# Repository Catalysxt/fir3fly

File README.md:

# fir3fly
This is an enlarged 4-digit 7-segment display. The motivation is to track my boxing sessions.

- [Interactive HTML BOM](https://Catalysxt.github.io/fir3fly/ibom_v2.html)

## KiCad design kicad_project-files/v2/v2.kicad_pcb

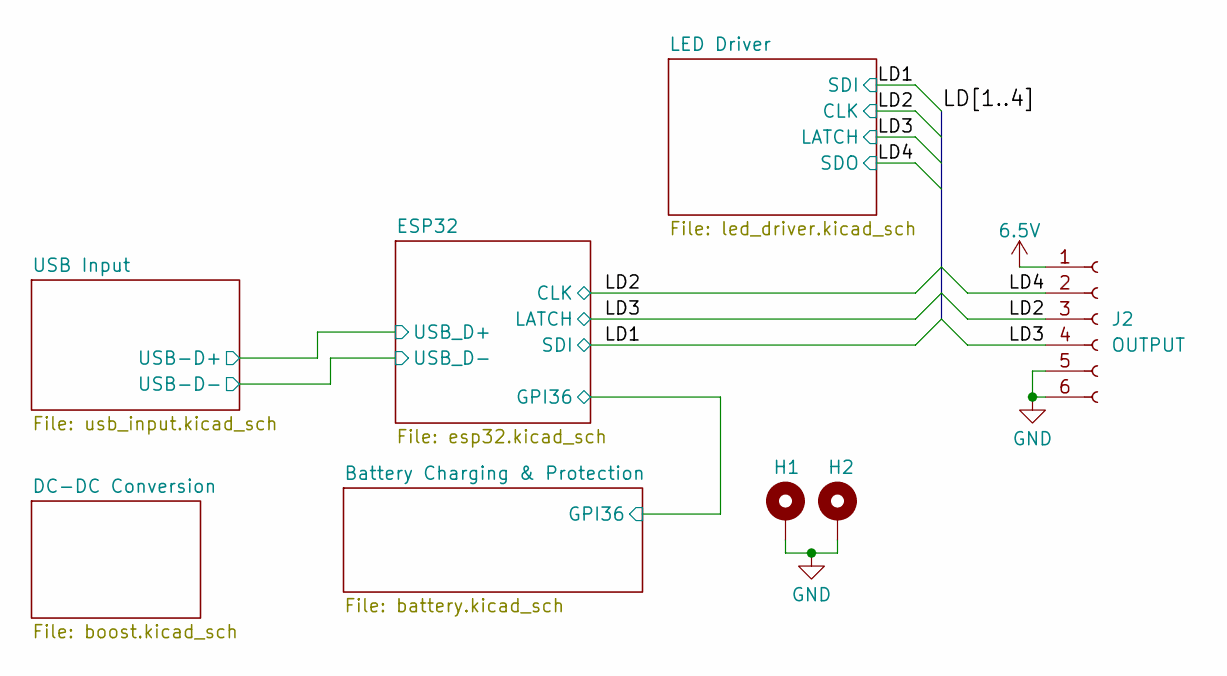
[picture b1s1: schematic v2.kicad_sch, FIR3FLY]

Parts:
H1, H2: MountingHole_Pad; MountingHole_2.5mm_Pad
J2: OUTPUT; PinSocket_1x06_P2.54mm_Horizontal

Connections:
/6.5V: J2.1
/LD2: J2.3; also elsewhere on the board
/LD3: J2.4; also elsewhere on the board
/LD4: J2.2; also elsewhere on the board
GND: H1.1 (1_1), H2.1 (1_1), J2.5, J2.6; also elsewhere on the board

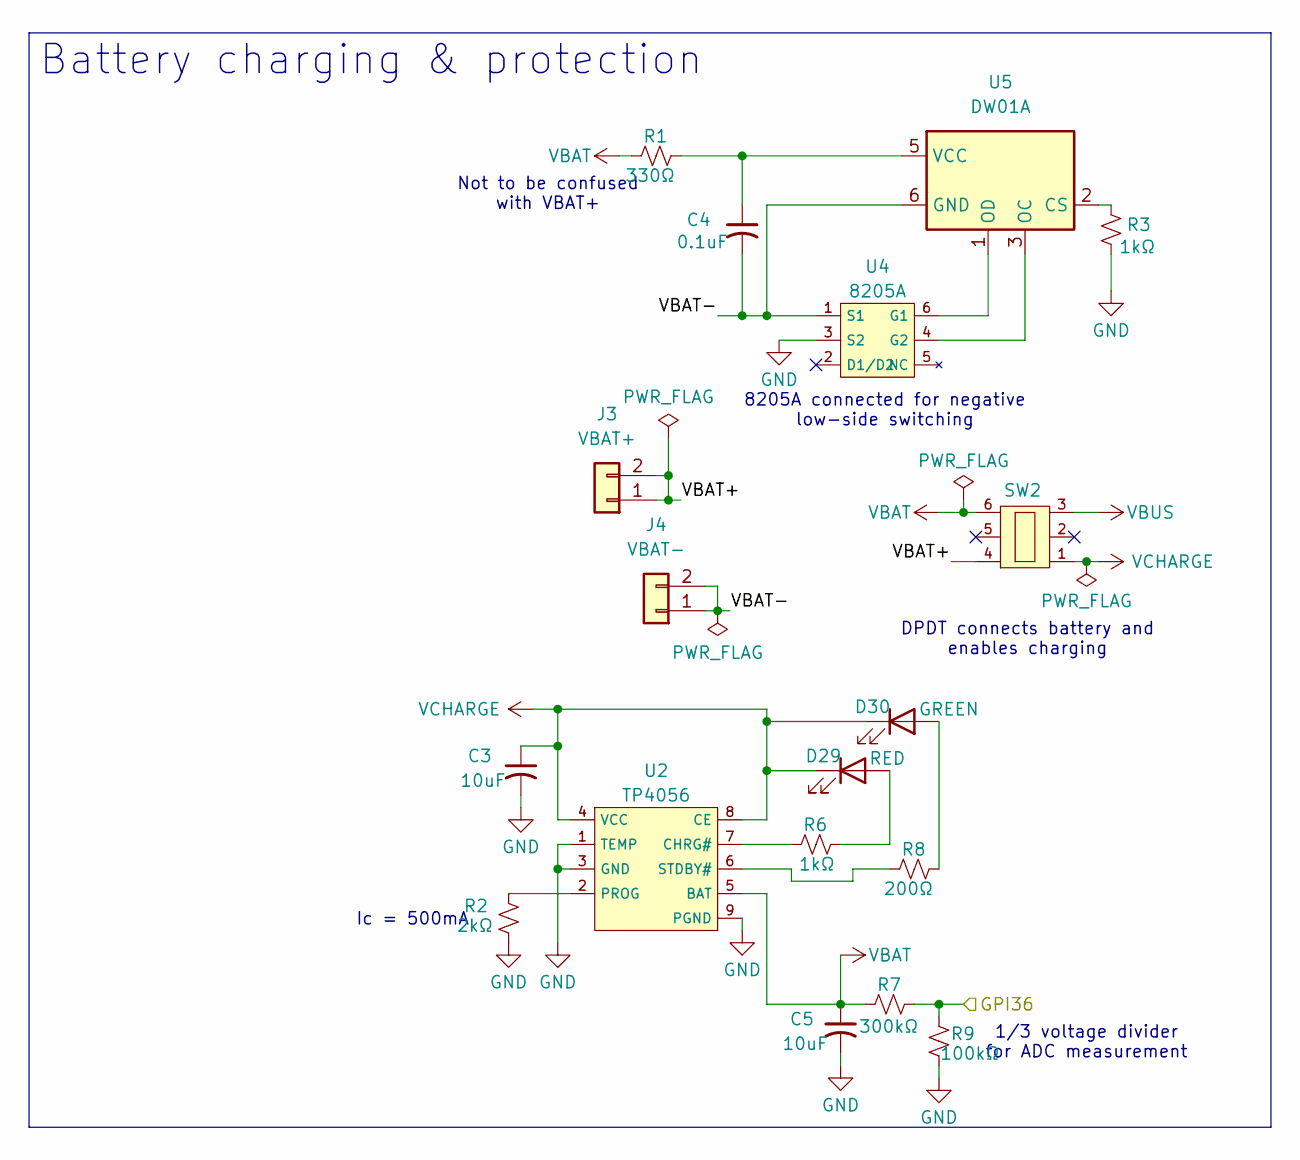
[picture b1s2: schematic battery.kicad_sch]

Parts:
C3, C5: 10uF; Taiyo Yuden TMK107BBJ106MA-T; Voltage Rating 25V; Part Type Basic; JLCPCB Part # C96446
C4: 0.1uF; C1206; Voltage Rating 50V; Part Type Basic; JLCPCB Part # C24497
D29: RED; LED_0805_Red; Part Type Basic; JLCPCB Part # C84256
D30: GREEN; LED_0805_Green; Part Type Extended; JLCPCB Part # C84260
J3: VBAT+; 18650 Battery Clip; Part Type Extended; JLCPCB Part # C2979182
J4: VBAT-; 18650 Battery Clip; Part Type Extended; JLCPCB Part # C2979182
R1: 330Ω; R_0603_1608Metric; Part Type Basic; JLCPCB Part # C23138
R2: 2kΩ; R_0603_1608Metric; Part Type Basic; JLCPCB Part # C22975
R3, R6: 1kΩ; R_0603_1608Metric; Part Type Basic; JLCPCB Part # C21190
R7: 300kΩ; R_0603_1608Metric; JLCPCB Part # C23024
R8: 200Ω; R_0603_1608Metric; Part Type Basic; JLCPCB Part # C8218
R9: 100kΩ; R_0603_1608Metric; Part Type Basic; JLCPCB Part # C25803
SW2: DPDT SW; Part Type Extended; JLCPCB Part # C22470282
U2: TP4056; ESOP-8_L4.9-W3.9-P1.27-LS6.0-BL-EP; Part Type Extended; LCSC Part # C5311018
U4: 8205A; 8205A_SOT-23-6_L2.9-W1.6-P0.95-LS2.8-BR; JLCPCB Part # C2762931
U5: DW01A; SOT-23-6

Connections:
/Battery Charging & Protection/GPI36: R7.2, R9.2; also elsewhere on the board
/Battery Charging & Protection/VBAT+: J3.1, J3.2, SW2.4
/Battery Charging & Protection/VBAT-: C4.2, J4.1, J4.2, U4.1 (S1), U5.6 (GND)
GND: C3.2, C5.2, R2.1, R3.2, R9.1, U2.1 (TEMP), U2.3 (GND), U2.9 (PGND), U4.3 (S2); also elsewhere on the board
unnamed: D29.2 (A), R6.2
unnamed: D30.2 (A), R8.2
unnamed: R6.1, U2.7 (CHRG#)
unnamed: R2.2, U2.2 (PROG)
unnamed: R8.1, U2.6 (STDBY#)
unnamed: U4.6 (G1), U5.1 (OD)
unnamed: U4.4 (G2), U5.3 (OC)
unnamed: R3.1, U5.2 (CS)
unnamed: C4.1, R1.2, U5.5 (VCC)
VBAT: C5.1, R1.1, R7.1, SW2.6, U2.5 (BAT); also elsewhere on the board
VBUS: SW2.3; also elsewhere on the board
VCHARGE: C3.1, D29.1 (K), D30.1 (K), SW2.1, U2.4 (VCC), U2.8 (CE)

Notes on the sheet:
8205A connected for negative low-side switching
DPDT connects battery and enables charging
Not to be confused with VBAT+
Ic = 500mA
1/3 voltage divider for ADC measurement
Battery charging & protection

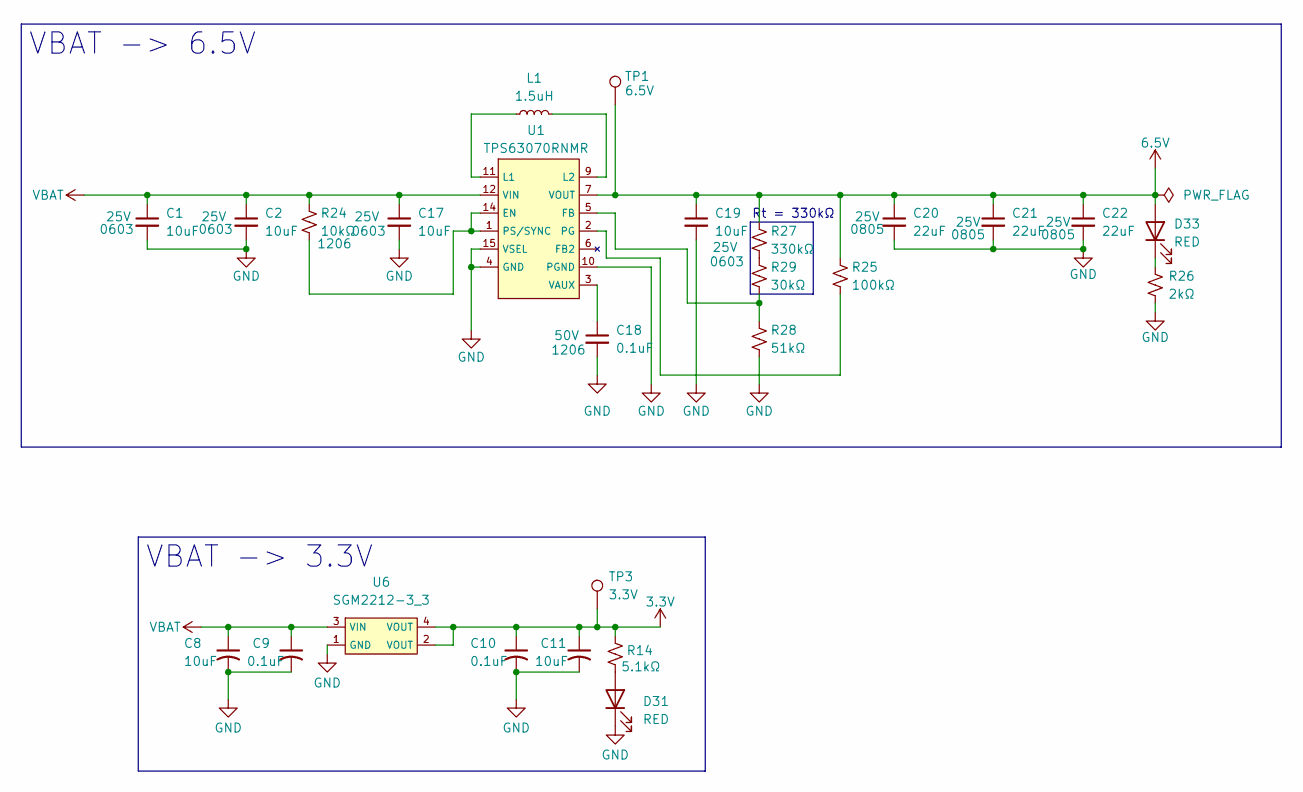
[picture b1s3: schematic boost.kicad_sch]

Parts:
C1, C2, C8, C11, C17, C19: 10uF; Taiyo Yuden TMK107BBJ106MA-T; Voltage Rating 25V; Part Type Basic; JLCPCB Part # C96446
C9, C10, C18: 0.1uF; C1206; Voltage Rating 50V; Part Type Basic; JLCPCB Part # C24497
C20, C21, C22: 22uF; C0805; Voltage Rating 25V; JLCPCB Part # C45783
D31, D33: RED; LED_0805_Red; Part Type Basic; JLCPCB Part # C84256
L1: 1.5uH; Coilcraft XFL4020-152MEC; Part Type Extended; JLCPCB Part # C3033018
R14: 5.1kΩ; R_0603_1608Metric; Part Type Basic; JLCPCB Part # C23186
R24: 10kΩ; R_0603_1608Metric; JLCPCB Part # C25804
R25: 100kΩ; R_0603_1608Metric; Part Type Basic; JLCPCB Part # C25803
R26: 2kΩ; R_0603_1608Metric
R27: 330kΩ; 0603_SMD; Part Type Basic; JLCPCB Part # C23137
R28: 51kΩ; 0603_SMD; Part Type Basic; JLCPCB Part # C23196
R29: 30kΩ; 0603_SMD; Part Type Basic; JLCPCB Part # C22984
TP1: 6.5V; TestPoint_Pad_D1.5mm
TP3: 3.3V; TestPoint_Pad_D1.5mm
U1: TPS63070RNMR; TPS63070; LCSC C109322
U6: SGM2212-3_3; SOT-223-3

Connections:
3.3V: C10.1, C11.1, R14.1, TP3.1 (1_1), U6.2 (VOUT), U6.4 (VOUT); also elsewhere on the board
6.5V: C19.1, C20.1, C21.1, C22.1, D33.2 (A), R25.1, R27.1, TP1.1 (1_1), U1.7 (VOUT); also elsewhere on the board
GND: C1.2, C2.2, C8.2, C9.2, C10.2, C11.2, C17.2, C18.2, C19.2, C20.2, C21.2, C22.2, D31.1 (K), R26.2, R28.2, U1.4 (GND), U1.10 (PGND), U1.15 (VSEL), U6.1 (GND); also elsewhere on the board
unnamed: D31.2 (A), R14.2
unnamed: D33.1 (K), R26.1
unnamed: R27.2, R29.1
unnamed: R24.2, U1.1 (PS/SYNC), U1.14 (EN)
unnamed: R28.1, R29.2, U1.5 (FB)
unnamed: L1.1, U1.11 (L1)
unnamed: L1.2, U1.9 (L2)
unnamed: R25.2, U1.2 (PG)
unnamed: C18.1, U1.3 (VAUX)
VBAT: C1.1, C2.1, C8.1, C9.1, C17.1, R24.1, U1.12 (VIN), U6.3 (VIN); also elsewhere on the board

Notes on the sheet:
Rt = 330kΩ
VBAT -> 3.3V
VBAT -> 6.5V

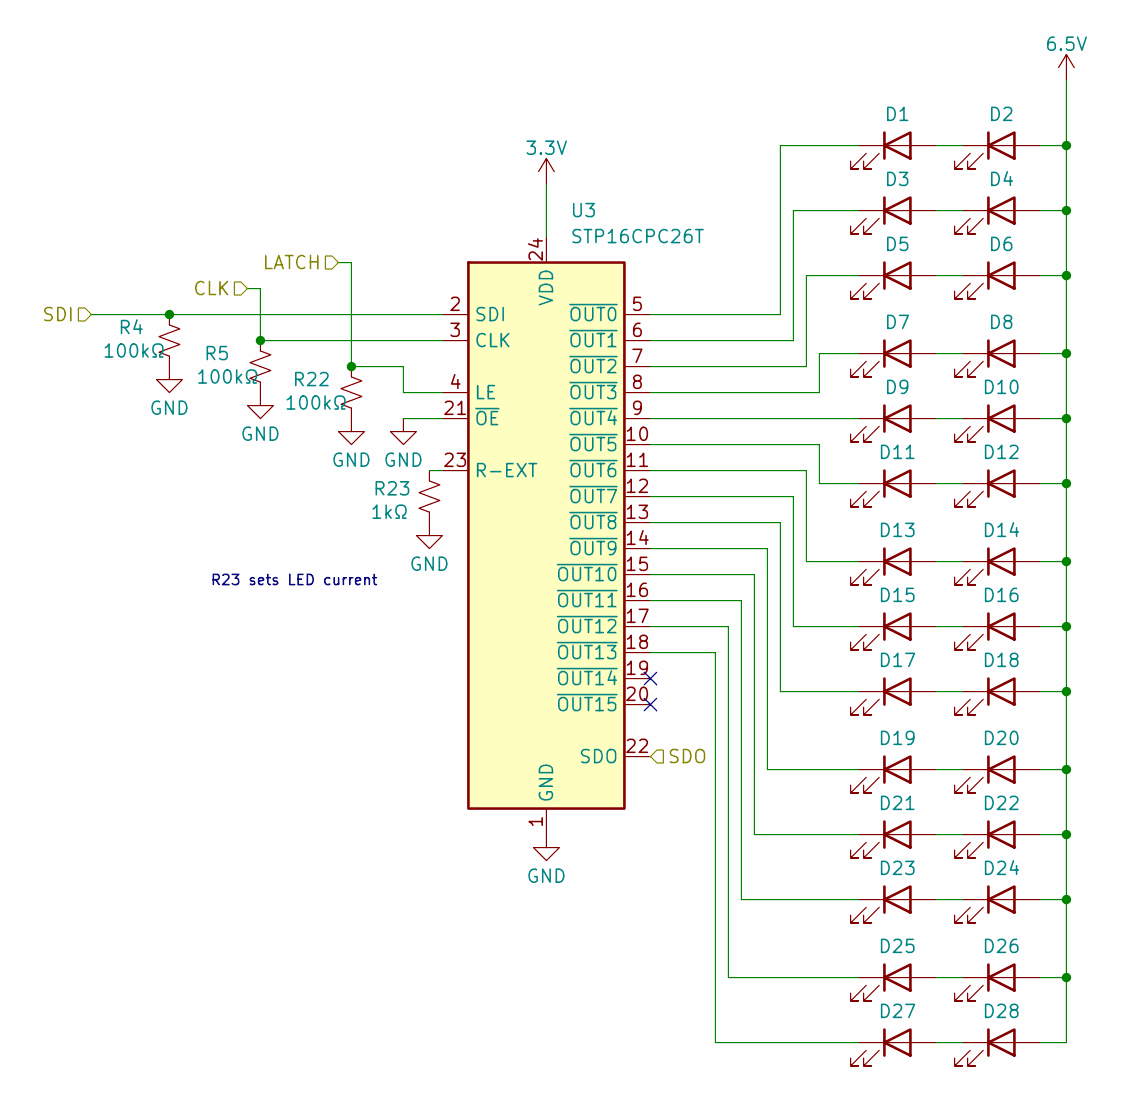
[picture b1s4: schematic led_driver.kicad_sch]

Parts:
D1: LED; LED-SMD_3P-L5.7-W3.0-RD; Part Type Extended; JLCPCB Part # C210347
D2, D3, D4, D5, D6, D7, D8, D9, D10, D11, D12, D13, D14, D15, D16, D17, D18, D19, D20, D21, D22, D23, D24, D25, D26, D27, D28: LED; LED-SMD_3P-L5.7-W3.0-RD; JLCPCB Part # C210347
R4, R5, R22: 100kΩ; R_0603_1608Metric; Part Type Basic; JLCPCB Part # C25803
R23: 1kΩ; R_0603_1608Metric; Part Type Basic; JLCPCB Part # C21190
U3: STP16CPC26T; TSSOP-24_4.4x7.8mm_P0.65mm

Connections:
3.3V: U3.24 (VDD); also elsewhere on the board
6.5V: D2.2 (A), D4.2 (A), D6.2 (A), D8.2 (A), D10.2 (A), D12.2 (A), D14.2 (A), D16.2 (A), D18.2 (A), D20.2 (A), D22.2 (A), D24.2 (A), D26.2 (A), D28.2 (A); also elsewhere on the board
/LD1: R4.1, U3.2 (SDI); also elsewhere on the board
/LD2: R5.1, U3.3 (CLK); also elsewhere on the board
/LD3: R22.1, U3.4 (LE); also elsewhere on the board
/LD4: U3.22 (SDO); also elsewhere on the board
GND: R4.2, R5.2, R22.2, R23.2, U3.1 (GND), U3.21 (~OE); also elsewhere on the board
unnamed: D1.2 (A), D2.1 (K)
unnamed: D1.1 (K), U3.5 (~OUT0)
unnamed: D3.2 (A), D4.1 (K)
unnamed: D3.1 (K), U3.6 (~OUT1)
unnamed: D5.2 (A), D6.1 (K)
unnamed: D5.1 (K), U3.7 (~OUT2)
unnamed: D7.2 (A), D8.1 (K)
unnamed: D7.1 (K), U3.8 (~OUT3)
unnamed: D9.1 (K), U3.9 (~OUT4)
unnamed: D9.2 (A), D10.1 (K)
unnamed: D11.2 (A), D12.1 (K)
unnamed: D11.1 (K), U3.10 (~OUT5)
unnamed: D13.2 (A), D14.1 (K)
unnamed: D13.1 (K), U3.11 (~OUT6)
unnamed: D15.2 (A), D16.1 (K)
unnamed: D15.1 (K), U3.12 (~OUT7)
unnamed: D17.2 (A), D18.1 (K)
unnamed: D17.1 (K), U3.13 (~OUT8)
unnamed: D19.2 (A), D20.1 (K)
unnamed: D19.1 (K), U3.14 (~OUT9)
unnamed: D21.2 (A), D22.1 (K)
unnamed: D21.1 (K), U3.15 (~OUT10)
unnamed: D23.2 (A), D24.1 (K)
unnamed: D23.1 (K), U3.16 (~OUT11)
unnamed: D25.2 (A), D26.1 (K)
unnamed: D25.1 (K), U3.17 (~OUT12)
unnamed: D27.2 (A), D28.1 (K)
unnamed: D27.1 (K), U3.18 (~OUT13)
unnamed: R23.1, U3.23 (R-EXT)

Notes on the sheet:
R23 sets LED current

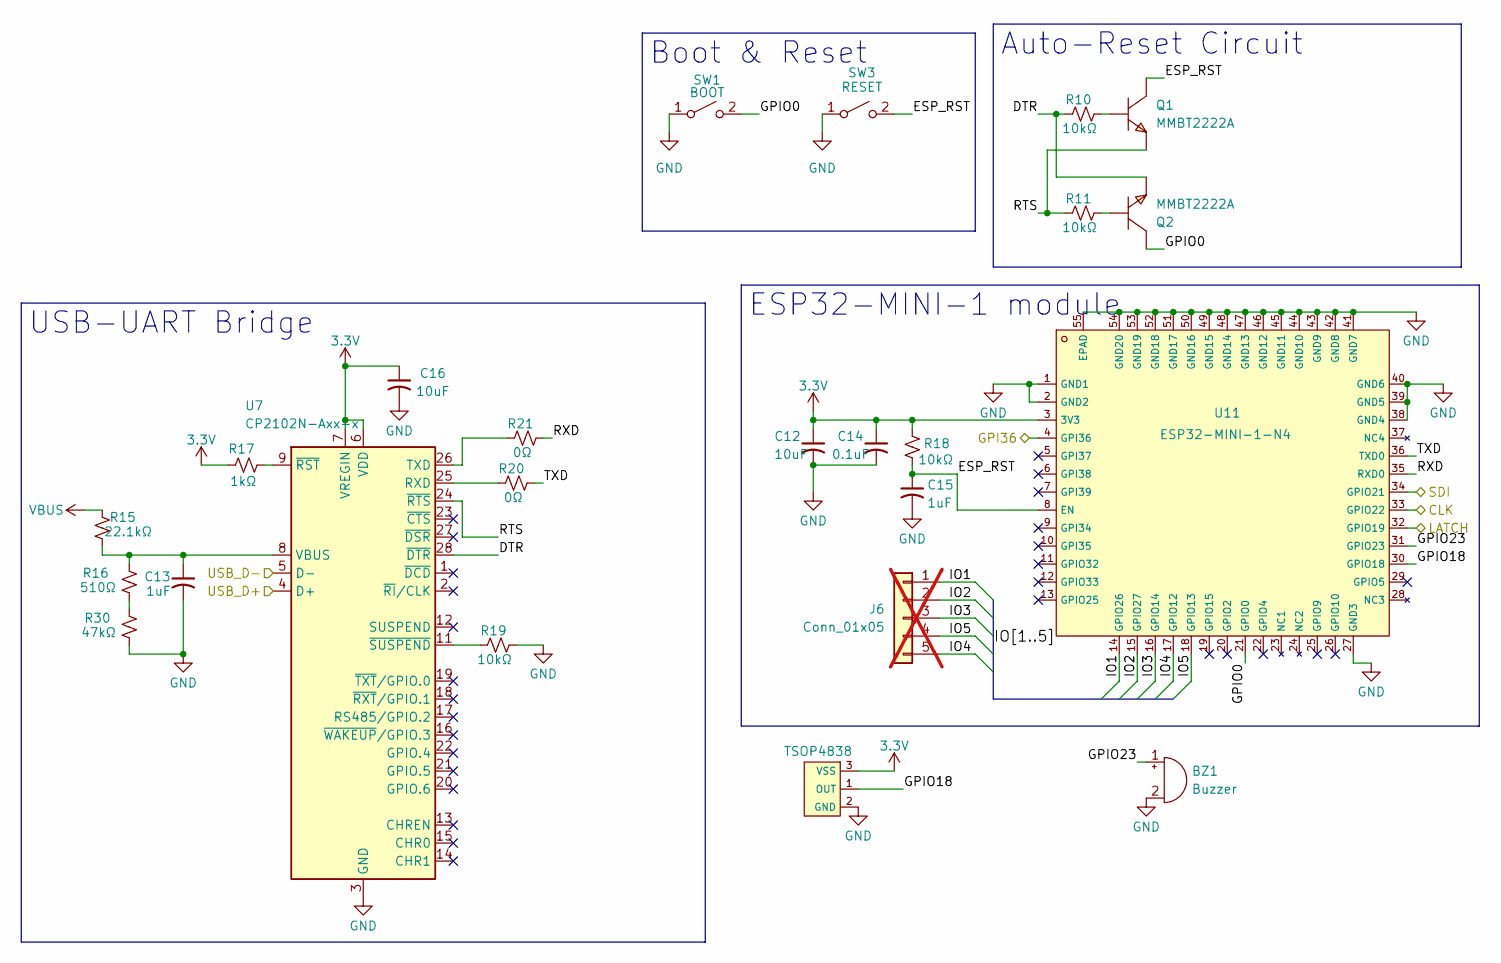
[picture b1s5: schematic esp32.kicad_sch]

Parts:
BZ1: Buzzer; BUZ-SMD_L9.6-W9.6-LS10.0-R; JLCPCB Part # C96127
C12, C16: 10uF; Taiyo Yuden TMK107BBJ106MA-T; Voltage Rating 25V; Part Type Basic; JLCPCB Part # C96446
C13, C15: 1uF; C1206; Voltage Rating 50V; Part Type Basic; JLCPCB Part # C1848
C14: 0.1uF; C1206; Voltage Rating 50V; Part Type Basic; JLCPCB Part # C24497
CGQ1: TSOP4838; JLCPCB Part # C124647
J6: Conn_01x05; PinSocket_1x05_P2.54mm_Vertical; not fitted
Q1, Q2: MMBT2222A; SOT-23-3_L2.9-W1.3-P1.90-LS2.4-BR; Part Type Basic; JLCPCB Part # C8512
R10, R11, R18: 10kΩ; R_0603_1608Metric; JLCPCB Part # C25804
R15: 22.1kΩ; R_0603_1608Metric; Part Type Basic; JLCPCB Part # C31850
R16: 510Ω; R_0603_1608Metric; Part Type Basic; JLCPCB Part # C23193
R17: 1kΩ; R_0603_1608Metric; Part Type Basic; JLCPCB Part # C21190
R19: 10kΩ; R_0603_1608Metric
R20, R21: 0Ω; 0603_SMD; Voltage Rating 0603; JLCPCB Part # C21189
R30: 47kΩ; R_0603_1608Metric; JLCPCB Part # C25819
SW1: BOOT; SW-SMD_L3.9-W3.0-P4.45; JLCPCB Part # C720477
SW3: RESET; SW-SMD_L3.9-W3.0-P4.45; JLCPCB Part # C720477
U7: CP2102N-Axx-x; QFN-28-1EP_5x5mm_P0.5mm_EP3.35x3.35mm
U11: ESP32-MINI-1-N4; ESP32-MINI-1 Module

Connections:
3.3V: C12.1, C14.1, C16.1, CGQ1.3 (VSS), R17.1, R18.1, U7.6 (VDD), U7.7 (VREGIN), U11.3 (3V3); also elsewhere on the board
/Battery Charging & Protection/GPI36: U11.4 (GPI36); also elsewhere on the board
/ESP32/DTR: Q2.2 (E), R10.1, U7.28 (~DTR)
/ESP32/ESP_RST: C15.1, Q1.3 (C), R18.2, SW3.2 (B), U11.8 (EN)
/ESP32/GPIO0: Q2.3 (C), SW1.2 (B), U11.21 (GPIO0)
/ESP32/GPIO18: CGQ1.1 (OUT), U11.30 (GPIO18)
/ESP32/GPIO23: BZ1.1 (+), U11.31 (GPIO23)
/ESP32/IO1: J6.1, U11.14 (GPIO26)
/ESP32/IO2: J6.2, U11.15 (GPIO27)
/ESP32/IO3: J6.3, U11.16 (GPIO14)
/ESP32/IO4: J6.5, U11.17 (GPIO12)
/ESP32/IO5: J6.4, U11.18 (GPIO13)
/ESP32/RTS: Q1.2 (E), R11.1, U7.24 (~RTS)
/ESP32/RXD: R21.2, U11.35 (RXD0)
/ESP32/TXD: R20.2, U11.36 (TXD0)
/ESP32/USB_D+: U7.4 (D+); also elsewhere on the board
/ESP32/USB_D-: U7.5 (D-); also elsewhere on the board
/LD1: U11.34 (GPIO21); also elsewhere on the board
/LD2: U11.33 (GPIO22); also elsewhere on the board
/LD3: U11.32 (GPIO19); also elsewhere on the board
GND: BZ1.2 (-), C12.2, C13.2, C14.2, C15.2, C16.2, CGQ1.2 (GND), R19.2, R30.1, SW1.1 (A), SW3.1 (A), U7.3 (GND), U7.29 (GND), U11.1 (GND1), U11.2 (GND2), U11.27 (GND3), U11.38 (GND4), U11.39 (GND5), U11.40 (GND6), U11.41 (GND7), U11.42 (GND8), U11.43 (GND9), U11.44 (GND10), U11.45 (GND11), U11.46 (GND12), U11.47 (GND13), U11.48 (GND14), U11.49 (GND15), U11.50 (GND16), U11.51 (GND17), U11.52 (GND18), U11.53 (GND19), U11.54 (GND20), U11.55 (EPAD); also elsewhere on the board
unnamed: Q1.1 (B), R10.2
unnamed: Q2.1 (B), R11.2
unnamed: R16.1, R30.2
unnamed: R20.1, U7.25 (RXD)
unnamed: R21.1, U7.26 (TXD)
unnamed: C13.1, R15.1, R16.2, U7.8 (VBUS)
unnamed: R17.2, U7.9 (~RST)
unnamed: R19.1, U7.11 (~SUSPEND)
VBUS: R15.2; also elsewhere on the board

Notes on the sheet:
Auto-Reset Circuit
ESP32-MINI-1 module
USB-UART Bridge
Boot & Reset

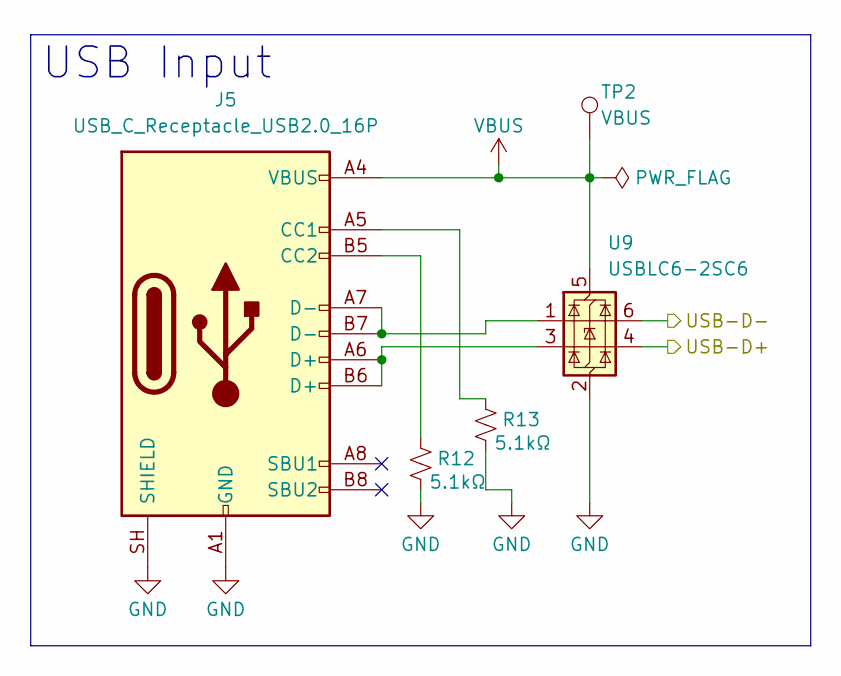
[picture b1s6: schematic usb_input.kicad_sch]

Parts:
J5: USB_C_Receptacle_USB2.0_16P; USB_C_Receptacle_GCT_USB4105-xx-A_16P_TopMnt_Horizontal
R12, R13: 5.1kΩ; R_0603_1608Metric; Part Type Basic; JLCPCB Part # C23186
TP2: VBUS; TestPoint_Pad_D1.5mm
U9: USBLC6-2SC6; SOT-23-6; Part Type Extended; JLCPCB Part # C7519

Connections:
/ESP32/USB_D+: U9.4 (I/O2); also elsewhere on the board
/ESP32/USB_D-: U9.6 (I/O1); also elsewhere on the board
GND: J5.A1 (GND), J5.A12 (GND), J5.B1 (GND), J5.B12 (GND), J5.SH (SHIELD), R12.2, R13.2, U9.2 (GND); also elsewhere on the board
unnamed: J5.A5 (CC1), R13.1
unnamed: J5.B5 (CC2), R12.1
unnamed: J5.A6 (D+), J5.B6 (D+), U9.3 (I/O2)
unnamed: J5.A7 (D-), J5.B7 (D-), U9.1 (I/O1)
VBUS: J5.A4 (VBUS), J5.A9 (VBUS), J5.B4 (VBUS), J5.B9 (VBUS), TP2.1 (1_1), U9.5 (VBUS); also elsewhere on the board

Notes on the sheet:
USB Input

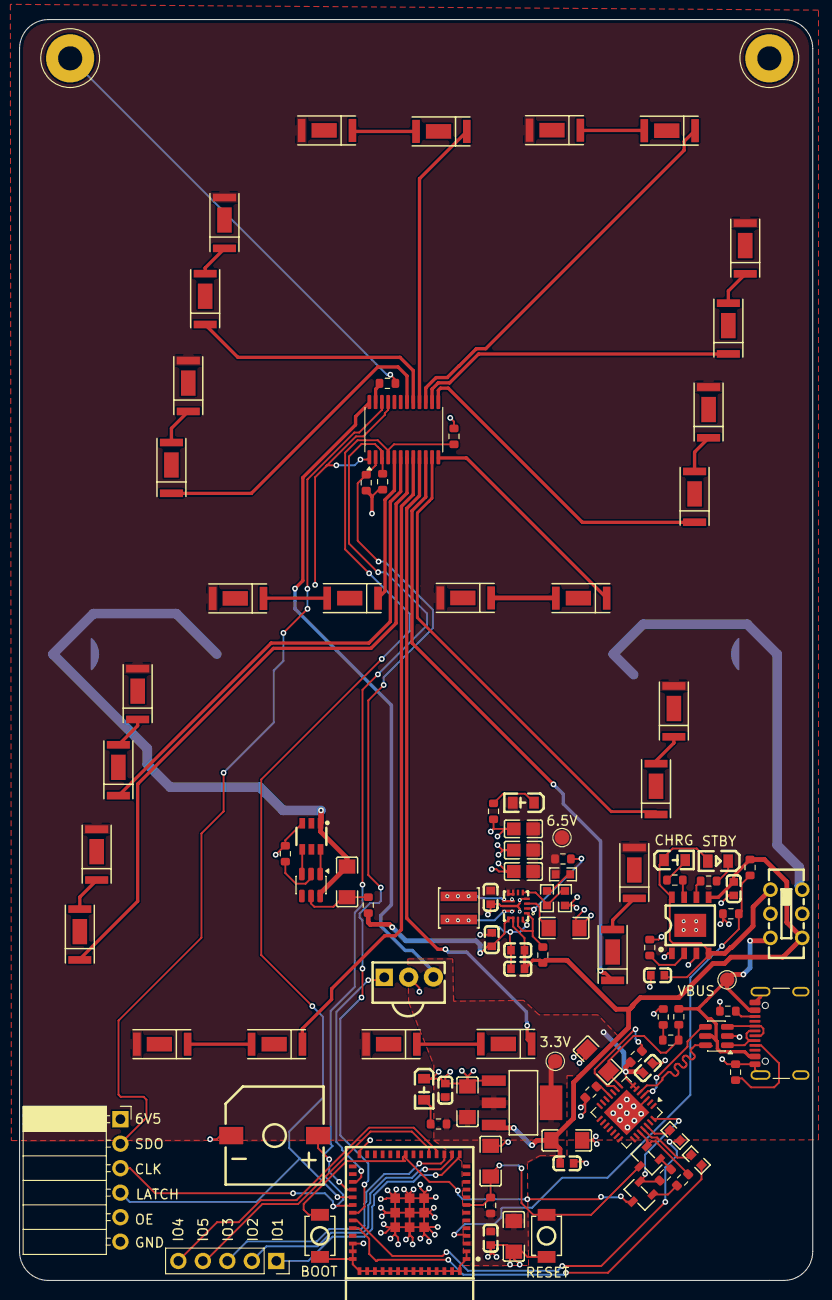
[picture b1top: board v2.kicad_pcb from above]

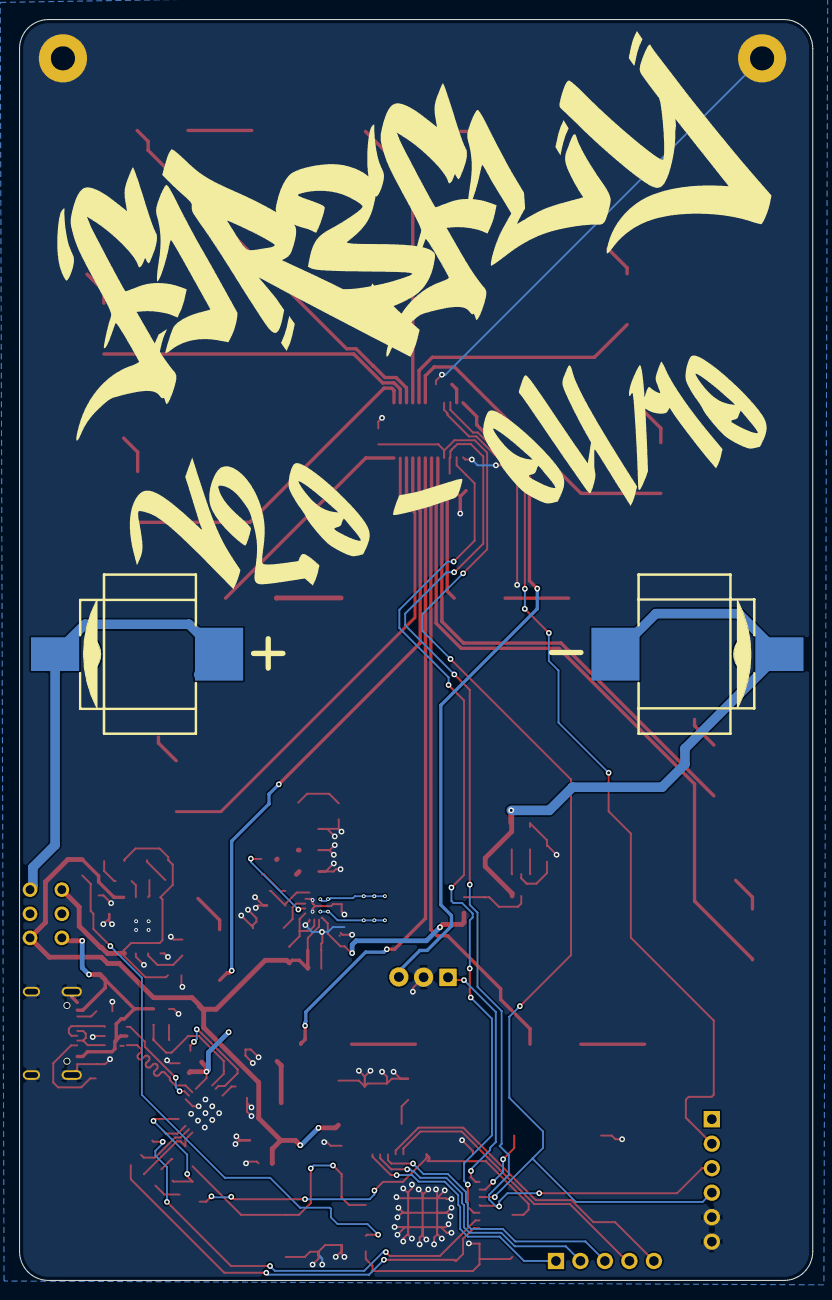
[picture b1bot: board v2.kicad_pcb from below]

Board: 2 copper layers, 82.2 x 130.8 mm, 109 parts (2 on the bottom side), 87 nets.
